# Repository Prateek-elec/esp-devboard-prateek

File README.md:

# ESP32-C3 Dev Board (KiCad) ⚡

A custom **ESP32-C3 development board** designed in **KiCad**, built for compact embedded prototyping with
**USB-C input, LiPo charging, stable 3.3V regulation**, and expansion headers for sensors/modules.

✅ Focus: **Embedded Hardware • PCB Design • Power + IO Integration**

---

## ✅ Key Features
- **ESP32-C3-WROOM module**
- **USB-C power input**
- **Single-cell LiPo charging circuit**
- **3.3V regulation** for stable MCU + peripherals
- **Boot / Reset circuit** for easy programming
- **GPIO breakout headers** for expansion
- Sensor/module support (example: **BME280**, mic amplifier, photo sensor)

---

## 📷 PCB Preview
### Top Layer

### Bottom Layer

---

## 📂 Repository Structure
```txt
esp-devboard-prateek/
│── README.md
│── LICENSE
│
├── hardware/
│   └── kicad/               # KiCad project files (.kicad_pro/.sch/.pcb)
│
├── docs/
│   ├── schematic.pdf        # Schematic export
│   └── pcb-renders/         # Top/Bottom/3D screenshots
│
└── fabrication/             # (optional) Gerbers, drill, BOM, PnP outputs

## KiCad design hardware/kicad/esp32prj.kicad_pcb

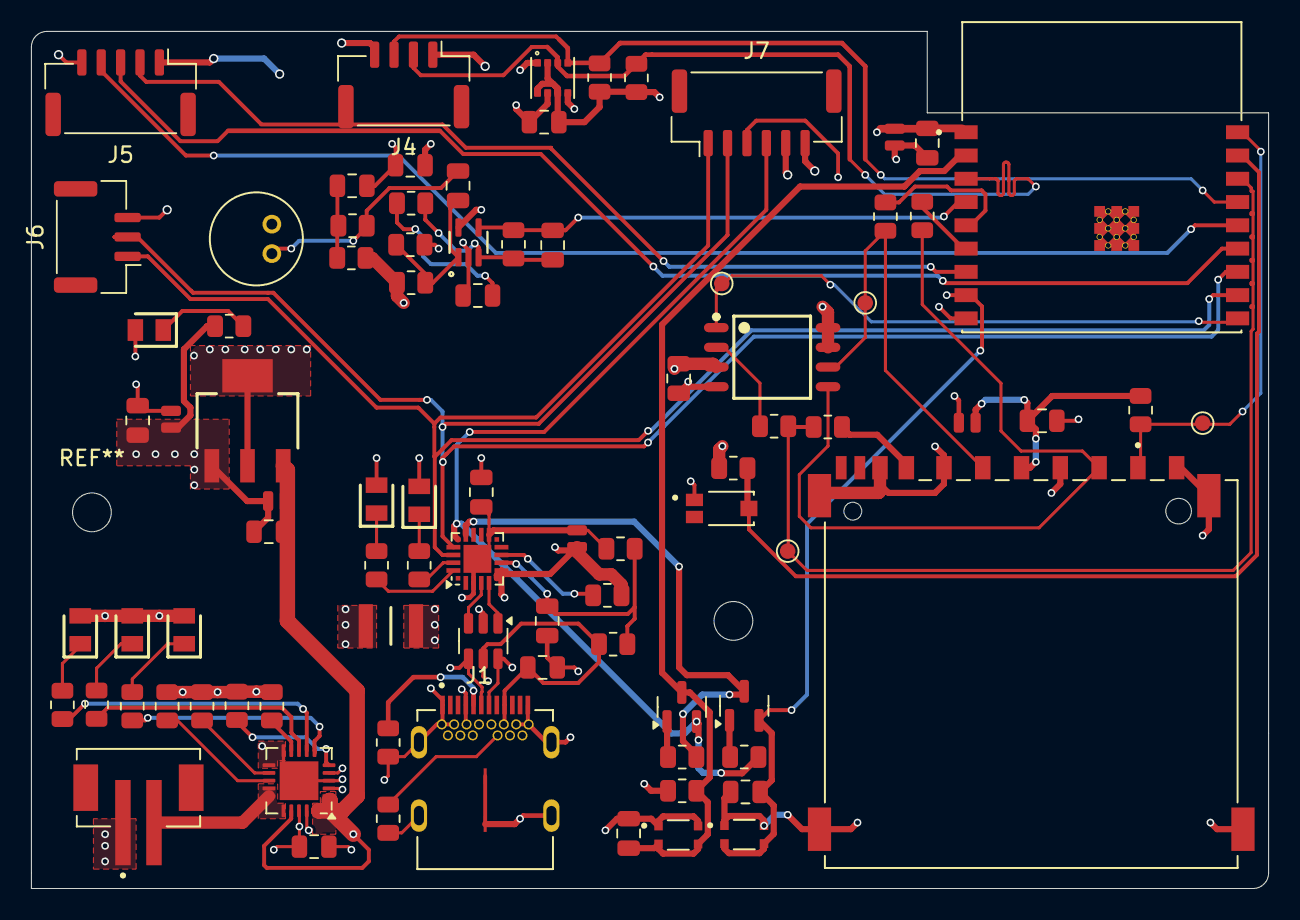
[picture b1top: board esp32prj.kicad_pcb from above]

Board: 4 copper layers, 79.8 x 55.2 mm, 86 parts (0 on the bottom side), 58 nets.

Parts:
C1, C2, C5, C8, C9, C10, C13, C14, C15, C16, C20, C21: 0.1u; C_0805_2012Metric
C3, C4, C7, C12: 10u; C_0504_1310Metric
C6: 1U; C_0805_2012Metric
C11: 1uf; C_0805_2012Metric
C17: 10u; C_0805_2012Metric
C19, C22: 1u; C_0805_2012Metric
C_9: 4.7u; C_0504_1310Metric
F1: 0ZCH0110AF2E; FUSC3226X100N
J1: SS-52400-002; BELFUSE_SS-52400-002
J2: B2B-PH-SM4-TB; JST_B2B-PH-SM4-TB
J3: GSD090012SEU; AMPHENOL_GSD090012SEU
J4: Conn_01x04_Pin; JST_GH_BM04B-GHS-TBT_1x04-1MP_P1.25mm_Vertical
J5: Conn_01x05_Pin; JST_GH_BM05B-GHS-TBT_1x05-1MP_P1.25mm_Vertical
J6: Conn_01x03_Pin; JST_GH_BM03B-GHS-TBT_1x03-1MP_P1.25mm_Vertical
J7: Conn_01x06; JST_GH_BM06B-GHS-TBT_1x06-1MP_P1.25mm_Vertical
LED1, LED4: LTST-C170KRKT; LEDC2012X120N
LED2, LED5: LTST-C170GKT; LEDC2012X120N
LED3, LED6: LTST-C170TBKT; LEDC2012X120N
MK1: CMC-5042PF-AC; CUI_CMC-5042PF-AC
Q1: TEMT6000X01; TRANS_TEMT6000X01
Q2, Q3: BC817; SOT-23
R1, R2, R19, R23, R30: 10K; R_0805_2012Metric
R3, R4: 5K1; R_0805_2012Metric
R5, R26, R28: 2K; R_0805_2012Metric
R6: 20K; R_0805_2012Metric
R7, R8, R9, R10, R14, R18: 470; R_0805_2012Metric
R11: 1k; R_0805_2012Metric
R12: 22K1; R_0805_2012Metric
R13: 47K5; R_0805_2012Metric
R15, R16, R20, R22: 50; R_0805_2012Metric
R17, R21, R33: 10k; R_0805_2012Metric
R24, R25: 4K7; R_0805_2012Metric
R27, R29: 1M; R_0805_2012Metric
R31: 100K; R_0805_2012Metric
S1: BOOT; SW_USLPT2819DT2TR
S2: RESET; SW_USLPT2819DT2TR
TP2: TestMISO; TestPoint_Pad_D1.0mm
TP3: TestSCLK; TestPoint_Pad_D1.0mm
TP4: TestCD_SD; TestPoint_Pad_D1.0mm
TP5: TestCS; TestPoint_Pad_D1.0mm
U1: ESP32-C3-WROOM-02-H4; MODULE_ESP32-C3-WROOM-02-H4
U2: MCP73871; QFN-20-1EP_4x4mm_P0.5mm_EP2.5x2.5mm
U3: BME280; PSON65P250X250X100-8N
U4: CP2102N-Axx-xQFN20; SiliconLabs_QFN-20-1EP_3x3mm_P0.5mm_EP1.8x1.8mm
U5: USBLC6-2SC6; SOT-23-6
U6: W25Q32JVSSIQ; SOIC127P790X216-8N
U7: MAX4466EXK; SOT65P210X110-5N
VR1: LM1117MPX-3.3; VREG_LM1117MPX-3.3

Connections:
+3.3V: C4.1, C5.1, C7.1, C8.1, C9.1, C10.2, C12.1, C13.1, C14.1, C15.1, C_9.1, J3.4 (VDD1), J4.1, J5.1, J7.5, LED4.2 (A), LED5.2 (A), LED6.2 (A), R11.1, R19.2, R21.2, R23.1, R24.1, R25.1, R26.2, R27.2, U1.1 (3V3), U3.2 (CSB), U3.6 (VDDIO), U3.8 (VDD), U4.6 (VDD), U4.7 (VREGIN), U6.3 (~WP(IO2)), U6.7 (~HOLD/~RESET(IO3)), U6.8 (VCC), U7.5 (VCC), VR1.2 (VOUT_2), VR1.4 (VOUT_4)
+5V: C2.1, C3.1, U2.1 (OUT), U2.17 (CE), U2.20 (OUT), VR1.3 (VIN)
/+5V_USB: C6.2, F1.2, LED1.2 (A), LED2.2 (A), LED3.2 (A), U2.2 (VPCC), U2.4 (PROG2), U2.18 (IN), U2.19 (IN)
/ESP32-C3-02/BOOT: C21.1, J7.3, Q3.2 (E), S1.3, S1.4, U1.8 (IO9)
/ESP32-C3-02/CD_SD: J3.1 (CD/DAT3), R19.1, TP4.1, U1.18 (IO0)
/ESP32-C3-02/CS: TP5.1, U1.10 (IO10), U6.1 (~CS)
/ESP32-C3-02/DTR: Q3.3 (C), R33.1, U4.15 (~CTS)
/ESP32-C3-02/EN: C22.1, Q2.3 (C), R21.1, S2.3, S2.4, U1.2 (EN)
/ESP32-C3-02/GPIO8: J5.2, U1.7 (IO8)
/ESP32-C3-02/GPIO18: J5.3, U1.13 (IO18)
/ESP32-C3-02/GPIO19: J5.4, U1.14 (IO19)
/ESP32-C3-02/MIC_OUT: C20.2, R31.2, U1.4 (IO5), U7.4 (OUT)
/ESP32-C3-02/MISO_D0: R16.2, R22.2, TP2.1, U1.16 (IO2)
/ESP32-C3-02/MOSI_D1: J3.2 (CMD), R15.2, U6.5 (DI(IO0))
/ESP32-C3-02/PHOTO_C: Q1.3, R23.2, U1.17 (IO1)
/ESP32-C3-02/RTS: J7.4, Q2.2 (E), R17.1, U4.16 (~RTS)
/ESP32-C3-02/RX_TX: J6.2, J7.2, U1.12 (TXD), U4.17 (RXD)
/ESP32-C3-02/SCL: J4.3, R24.2, U1.15 (IO3), U3.4 (SCK)
/ESP32-C3-02/SCLK: J3.5 (CLK), R20.1, TP3.1, U6.6 (CLK)
/ESP32-C3-02/SDA: J4.2, R25.2, U1.3 (IO4), U3.3 (SDI)
/ESP32-C3-02/TX_RX: J6.1, J7.1, U1.11 (RXD), U4.18 (TXD)
/ESP32-C3-02/USB_D+: U4.4 (D+), U5.3 (I/O2)
/ESP32-C3-02/USB_D-: U4.5 (D-), U5.1 (I/O1)
/PWN_LED: LED4.1 (K), R10.2
/USB_DN: J1.A7 (DN1), J1.B7 (DN2), U5.6 (I/O1)
/USB_DP: J1.A6 (DP1), J1.B6 (DP2), U5.4 (I/O2)
/VBAT: J2.2, U2.14 (V_{BAT}), U2.15 (V_{BAT}), U2.16 (V_{BAT_SENSE})
/VBUS: C1.1, F1.1, J1.A4 (VBUSA1), J1.A9 (VBUSA2), J1.B4 (VBUSB1), J1.B9 (VBUSB2), R12.1, U5.5 (VBUS)
/charged: R8.1, U2.8 (STAT1/~LBO)
/charging: R9.1, U2.6 (~PG)
/charging_power_good: R7.1, U2.7 (STAT2)
GND: C1.2, C2.2, C3.2, C4.2, C5.2, C6.1, C7.2, C8.2, C9.2, C10.1, C11.2, C12.2, C13.2, C14.2, C15.2, C16.1, C19.2, C21.2, C22.2, C_9.2, J1.A1 (GNDA1), J1.A12 (GNDA2), J1.B1 (GNDB1), J1.B12 (GNDB2), J1.G1 (GND/SHIELD), J1.G2 (GND/SHIELD), J1.G3 (GND/SHIELD), J1.G4 (GND/SHIELD), J1.S1 (GND/SHIELD), J1.S2 (GND/SHIELD), J1.S3 (GND/SHIELD), J1.S4 (GND/SHIELD), J2.1, J3.3 (VSS1), J3.6 (VSS2), J3.8 (DAT1), J3.9 (DAT2), J3.G1 (SHIELD_GND), J3.G2 (SHIELD_GND), J3.G3 (SHIELD_GND), J3.G4 (SHIELD_GND), J4.4, J5.5, J6.3, J7.6, MK1.GND, Q1.1, R1.1, R2.1, R3.2, R4.2, R5.2, R6.2, R10.1, R13.2, R29.1, S1.1, S1.2, S2.1, S2.2, U1.9 (GND), U1.19 (GND), U1.20 (GND), U1.21 (GND), U1.22 (GND), U1.23 (GND), U1.24 (GND), U1.25 (GND), U1.26 (GND), U1.27 (GND), U1.28 (GND), U1.29 (GND), U1.30 (GND), U1.31 (GND), U1.32 (GND), U1.33 (GND), U1.34 (GND), U1.35 (GND), U1.36 (GND), U1.37 (GND), U1.38 (GND), U1.39 (GND), U2.3 (SEL), U2.10 (V_{SS}), U2.11 (V_{SS}), U2.21 (V_{SS}), U3.1 (GND), U3.5 (SDO), U3.7 (GND), U4.3 (GND), U4.12 (GND), U4.21 (GND), U5.2 (GND), U6.4 (GND), U7.2 (GND), VR1.1 (GND)
unnamed: C16.2, R26.1, R28.2
unnamed: C17.1, MK1.OUT, R28.1
unnamed: C19.1, R30.1
unnamed: J1.A5 (CC1), R4.1
unnamed: J1.B5 (CC2), R3.1
unnamed: J3.7 (DAT0), R16.1
unnamed: LED1.1 (K), R7.2
unnamed: LED2.1 (K), R8.2
unnamed: LED3.1 (K), R9.2
unnamed: LED5.1 (K), R18.2
unnamed: LED6.1 (K), R14.2
unnamed: Q2.1 (B), R33.2
unnamed: Q3.1 (B), R17.2
unnamed: R20.2, U1.5 (IO6)
unnamed: R15.1, U1.6 (IO7)
unnamed: R5.1, U2.13 (PROG1)
unnamed: R6.1, U2.12 (PROG3)
unnamed: R1.2, U2.5 (THERM)
unnamed: R2.2, U2.9 (~TE)
unnamed: C11.1, R12.2, R13.1, U4.8 (VBUS)
unnamed: R11.2, U4.9 (~RST)
unnamed: R18.1, U4.19 (~RXT/GPIO.3)
unnamed: R14.1, U4.20 (~TXT/GPIO.2)
unnamed: R22.1, U6.2 (DO(IO1))
unnamed: C17.2, R27.1, R29.2, U7.1 (IN+)
unnamed: C20.1, R30.2, R31.1, U7.3 (IN-)
